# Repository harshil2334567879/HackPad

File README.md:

# HackPad

Hi! This is my first custom macropad that I made for the Hack Club HackPad program.

I designed the PCB myself in KiCad and learned how to make a schematic, assign footprints, route the PCB, add copper pours, fix DRC errors, and generate the manufacturing files. Before this project I had never designed a PCB, so this was a great learning experience.

## Features

- 6 Mechanical Keys
- Rotary Encoder
- 0.91" OLED Display
- 7 SK6812 MINI-E RGB LEDs
- Seeed Studio XIAO RP2040
- Fully programmable with KMK/QMK

## Why I Made It

I wanted to learn PCB design and build something that I could actually use on my desk. Instead of buying a macropad, I thought it would be much more fun to make one from scratch.

This project helped me understand how electronic components are connected, how PCB routing works, and how a custom keyboard is designed.

## Challenges

The hardest part was routing the PCB and fitting everything in a compact layout. I had to move components around multiple times before I got a clean design. Understanding footprints and PCB rules was also confusing at first, but I figured it out while working on the project.

## What I Learned

- KiCad basics
- PCB routing
- Schematics
- Copper pours
- Design Rule Check (DRC)
- PCB manufacturing process

## Images

(Add screenshots or renders here)

## Files

- PCB Design
- Schematic
- Gerber Files
- Firmware
- Case Design (if applicable)

## Future Improvements

- Better RGB effects
- More firmware features
- Custom keycaps
- 3D printed case

## Thanks

Thanks to Hack Club for creating the HackPad program and providing the resources that helped me build my first custom PCB. It was a really fun project and I learned a lot from it.

Published by Harshil

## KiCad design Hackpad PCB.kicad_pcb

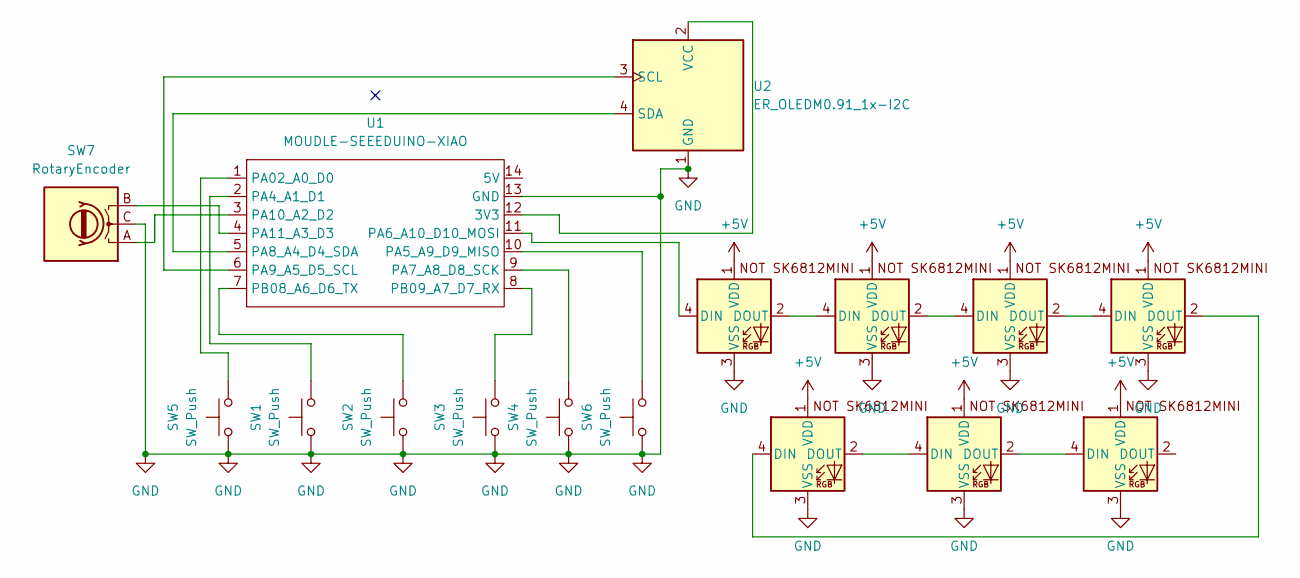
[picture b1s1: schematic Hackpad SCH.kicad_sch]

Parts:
D1, D2, D3, D4, D5, D6, D7: SK6812MINI-E; SK6812MINI-E_fixed
SW1, SW2, SW3, SW4, SW5, SW6: SW_Push; SW_Cherry_MX_1.00u_PCB
SW7: RotaryEncoder; RotaryEncoder_Alps_EC11E-Switch_Vertical_H20mm_MountingHoles
U1: MOUDLE-SEEEDUINO-XIAO; XIAO-Generic-Hybrid-14P-2.54-21X17.8MM
U2: ER_OLEDM0.91_1x-I2C

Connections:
+5V: D1.1 (VDD), D2.1 (VDD), D3.1 (VDD), D4.1 (VDD), D5.1 (VDD), D6.1 (VDD), D7.1 (VDD); also elsewhere on the board
GND: D1.3 (VSS), D2.3 (VSS), D3.3 (VSS), D4.3 (VSS), D5.3 (VSS), D6.3 (VSS), D7.3 (VSS), SW1.1, SW2.1, SW3.1, SW4.1, SW5.1, SW6.1, SW7.C, U1.13 (GND), U2.1 (GND); also elsewhere on the board
unnamed 2: D1.4 (DIN), U1.11 (PA6_A10_D10_MOSI); also elsewhere on the board
unnamed 3: D1.2 (DOUT), D2.4 (DIN); also elsewhere on the board
unnamed: D2.2 (DOUT), D3.4 (DIN)
unnamed: D3.2 (DOUT), D4.4 (DIN)
unnamed: D4.2 (DOUT), D5.4 (DIN)
unnamed: D5.2 (DOUT), D6.4 (DIN)
unnamed: D6.2 (DOUT), D7.4 (DIN)
unnamed: U1.12 (3V3), U2.2 (VCC)
unnamed: SW5.2, U1.1 (PA02_A0_D0)
unnamed: SW1.2, U1.2 (PA4_A1_D1)
unnamed: SW6.2, U1.10 (PA5_A9_D9_MISO)
unnamed: SW4.2, U1.9 (PA7_A8_D8_SCK)
unnamed: U1.5 (PA8_A4_D4_SDA), U2.4 (SDA)
unnamed: U1.6 (PA9_A5_D5_SCL), U2.3 (SCL)
unnamed: SW7.A, U1.3 (PA10_A2_D2)
unnamed: SW7.B, U1.4 (PA11_A3_D3)
unnamed: SW2.2, U1.7 (PB08_A6_D6_TX)
unnamed: SW3.2, U1.8 (PB09_A7_D7_RX)

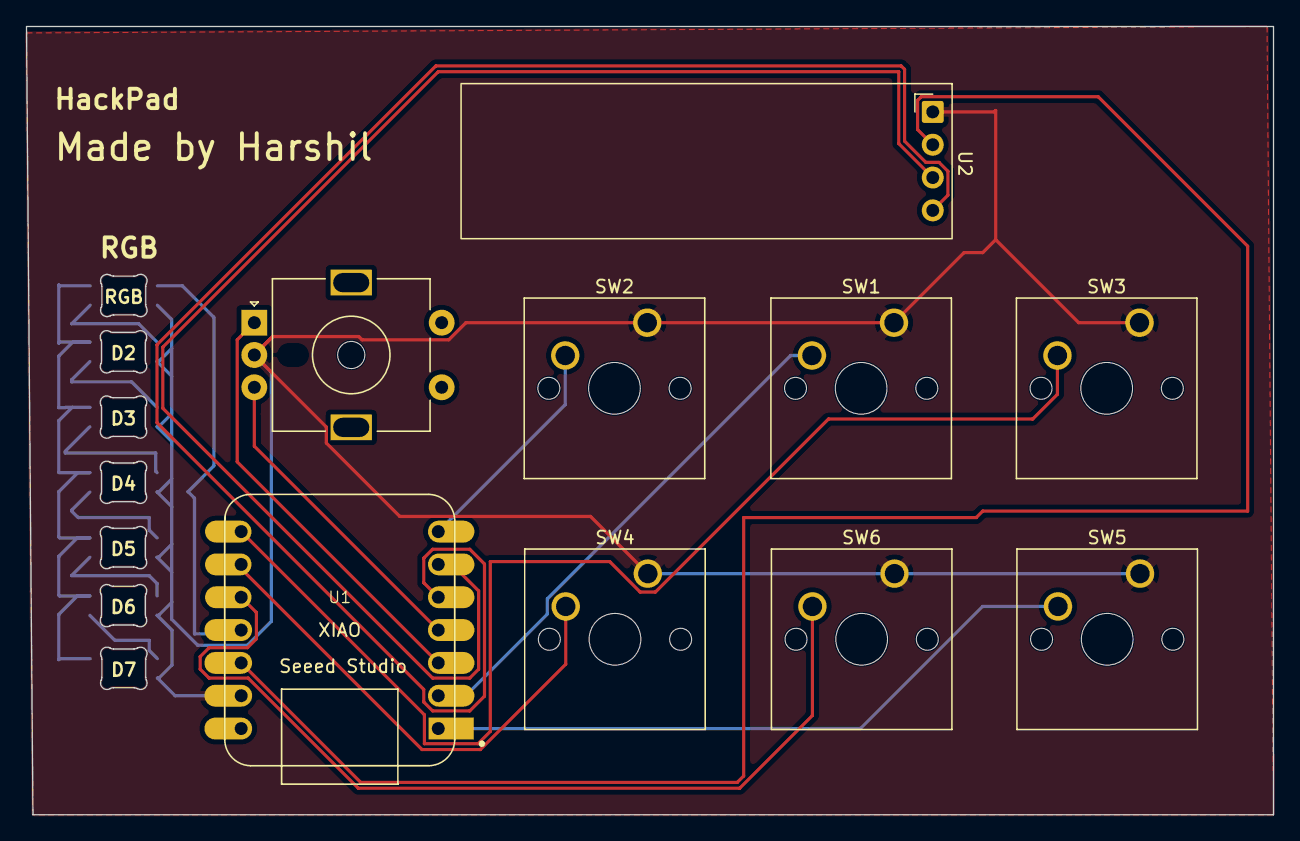
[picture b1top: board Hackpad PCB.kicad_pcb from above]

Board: 2 copper layers, 96.5 x 61.0 mm, 16 parts (0 on the bottom side), 20 nets.

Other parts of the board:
RGB: SK6812MINI-E; SK6812MINI-E_fixed

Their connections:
+5V: RGB.1 (VDD); also elsewhere on the board
GND: RGB.3 (VSS); also elsewhere on the board
unnamed 2: RGB.4 (DIN); also elsewhere on the board
unnamed 3: RGB.2 (DOUT); also elsewhere on the board
